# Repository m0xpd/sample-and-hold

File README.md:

# S&H
A Sample and Hold for Eurorack, based on the LF398

This repository describes a simple sample & hold module, developed for electronic synthesisers, in Eurorack format, based on the
[LF398](https://www.ti.com/lit/gpn/lf398-n) device. 

**Functional Description**

S&H is designed to be a simple, "no frills" sample and hold. It just detects a rising edge on the TRIGGER input and samples the 
voltage applied to INPUT at the point of this edge and holds on OUTPUT until the next triggering event. There is a GATE output, 
which is asserted for as long as the TRIGGER signal is high and an internal clock, which generates a trigger stream normalled 
to the edge detection circuits when nothing else is plugged into the TRIGGER input.

**Licensing**

S&H is published under a Creative Commons BY-SA 4.0 [License](https://github.com/m0xpd/encore/blob/main/LICENSE.txt)

**Implementation**

The system is implemented on a single PCB.

The schematic for the system is linked by the graphic below below (click for the full-size schematic):

**Specifications**

S&H is 6HP wide and extends 30mm behind the front panel (when a standard Eurorack power header is inserted).

S&H draws <9 mA (typically 5mA) from the +12V supply and <6 mA (typically 3mA) from the -12V supply.

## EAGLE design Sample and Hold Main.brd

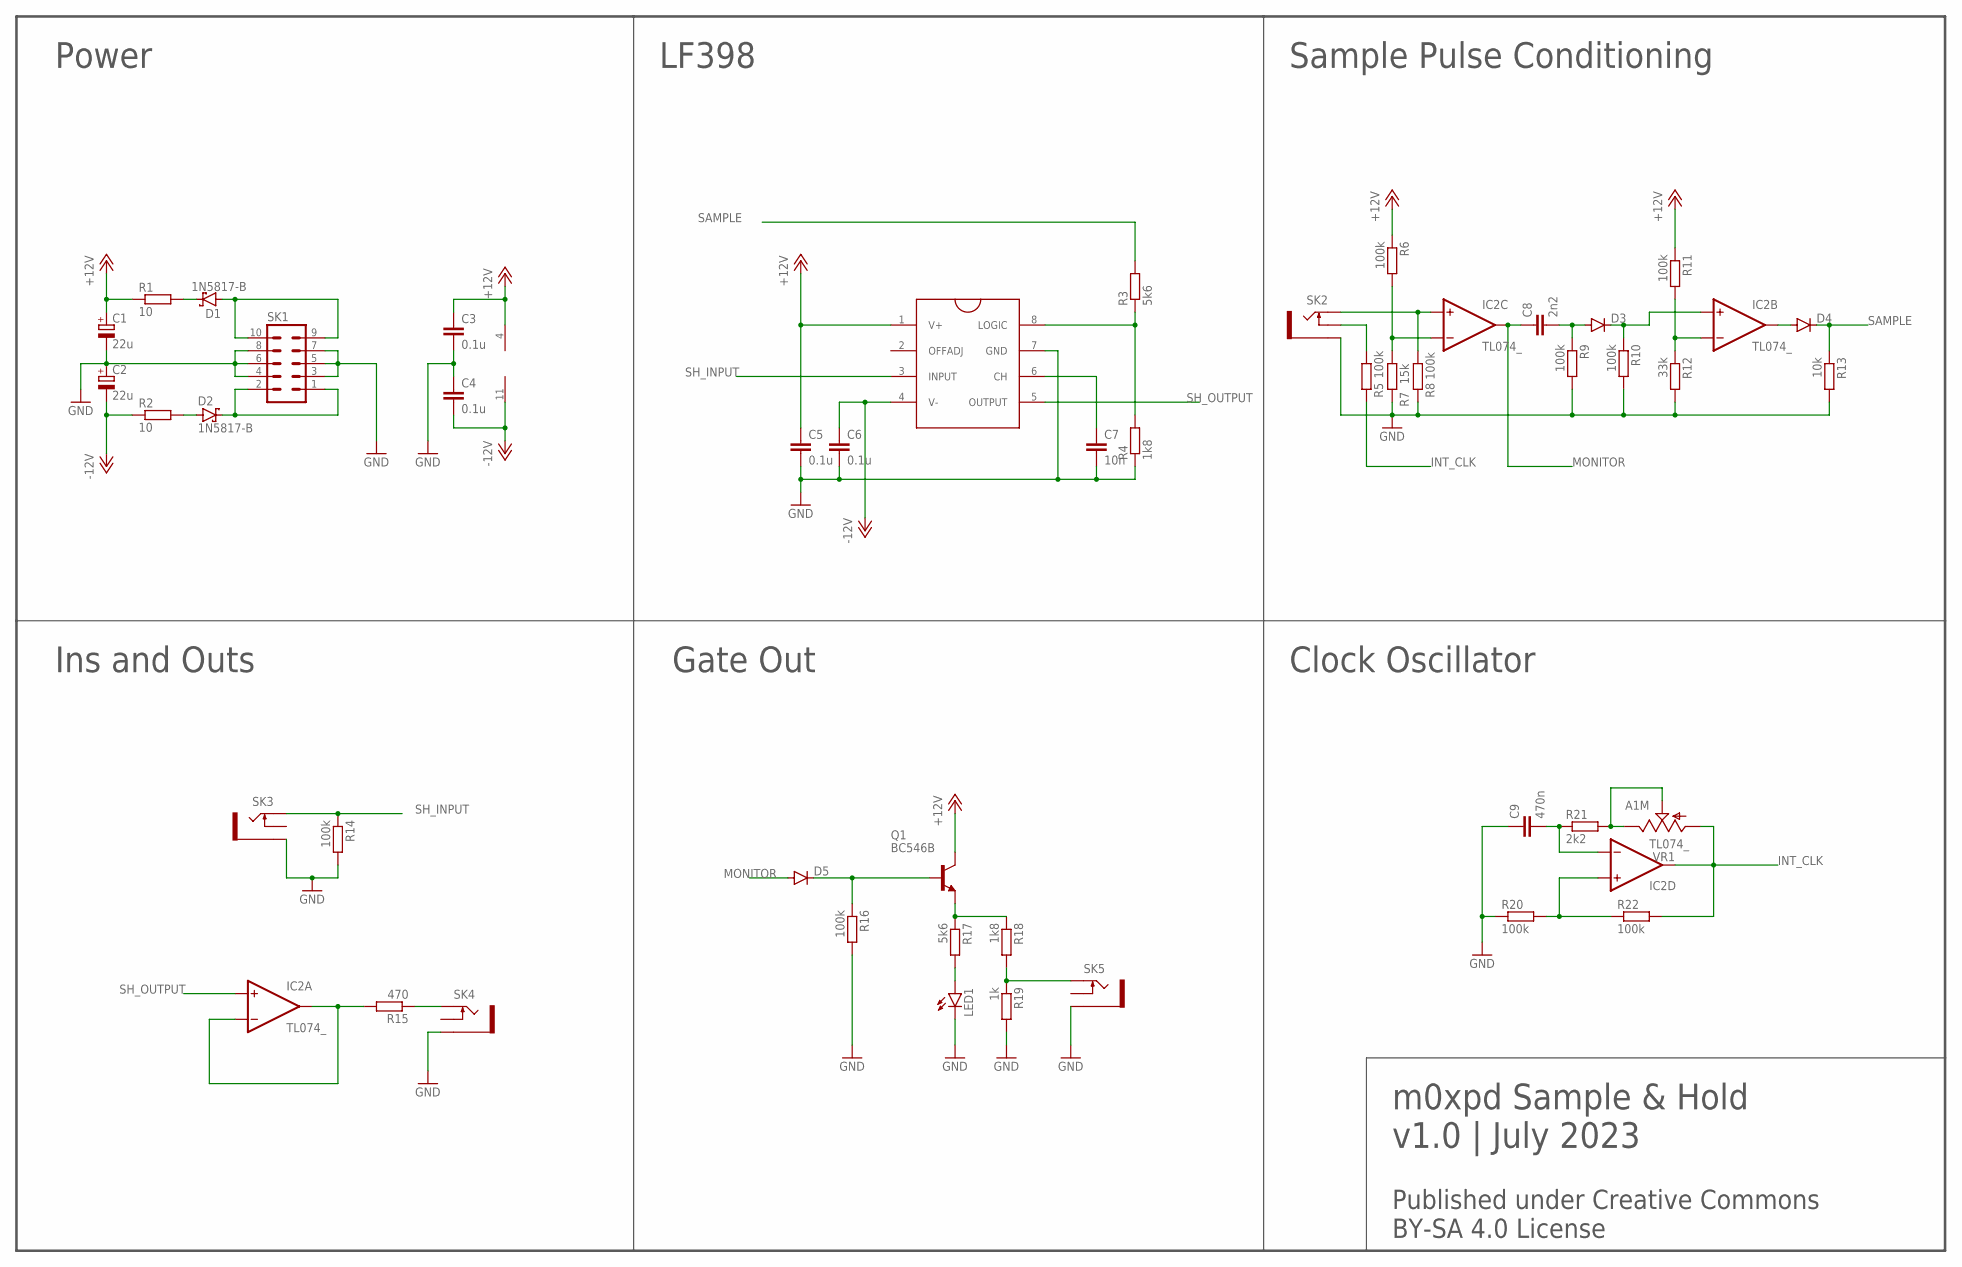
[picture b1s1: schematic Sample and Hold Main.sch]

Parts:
C1, C2: 22u; E2,5-6
C3, C4, C5, C6: 0.1u; C050-024X044
C7: 10n; C050-025X075
C8: 2n2; C050-024X044
C9: 470n; C050-035X075
D1, D2: 1N5817-B; DO41-7.6
D3, D4, D5: 1N4148DO35-7; DO35-7
IC1: LF398; DIL08
IC2: TL074_; DIL14
LED1: LED3MM
Q1: BC546B; TO92-EBC
R1, R2: 10; 0204/7
R3, R17: 5k6; 0204/7
R4, R18: 1k8; 0204/7
R5, R6, R8, R9, R10, R11, R14, R16, R20, R22: 100k; 0204/7
R7: 15k; 0204/7
R12: 33k; 0204/7
R13: 10k; 0204/7
R15: 470; 0204/7
R19: 1k; 0204/7
R21: 2k2; 0204/7
SK1: EURO_POWER_HEADERFAT_PADS; EURO_PWR_HEADER_FAT
SK2, SK3, SK4, SK5: THONKICONNNEW; WQP-PJ301M-12_JACK
VR1: A1M; 9MM_SNAP-IN_POT

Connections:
+12V: C1.+, C3.1, C5.1, IC1.1 (V+), IC2.4 (V+), Q1.C, R1.1, R6.1, R11.1
-12V: C2.-, C4.2, C6.1, IC1.4 (V-), IC2.11 (V-), R2.1
GND: C1.-, C2.+, C3.2, C4.1, C5.2, C6.2, C7.2, C9.1, IC1.7 (GND), LED1.K (C), R4.1, R7.2, R8.2, R9.2, R10.2, R12.2, R13.2, R14.2, R16.2, R19.2, R20.1, SK1.3, SK1.4, SK1.5, SK1.6, SK1.7, SK1.8, SK2.P$3_SLEEVE (SLEEVE), SK3.P$3_SLEEVE (SLEEVE), SK4.P$3_SLEEVE (SLEEVE), SK5.P$3_SLEEVE (SLEEVE)
INT_CLK: IC2.14 (OUT), R5.2, R22.2, VR1.1 (A)
MONITOR: C8.1, D5.A, IC2.8 (OUT)
unnamed: IC2.1 (OUT), IC2.2 (-IN), R15.2
unnamed: IC2.9 (-IN), R6.2, R7.1
unnamed: R15.1, SK4.P$1_TIP (TIP)
unnamed: C7.1, IC1.6 (CH)
unnamed: IC2.10 (+IN), R8.1, SK2.P$1_TIP (TIP)
unnamed: IC1.8 (LOGIC), R3.1, R4.2
unnamed: Q1.E, R17.1, R18.1
unnamed: C8.2, D3.A, R9.1
unnamed: D3.C, IC2.5 (+IN), R10.1
unnamed: LED1.A, R17.2
unnamed: IC2.6 (-IN), R11.2, R12.1
unnamed: D4.A, IC2.7 (OUT)
unnamed: C9.2, IC2.13 (-IN), R21.1
unnamed: IC2.12 (+IN), R20.2, R22.1
unnamed: D5.C, Q1.B, R16.1
unnamed: R21.2, VR1.2 (S), VR1.3 (E)
unnamed: R5.1, SK2.P$2_SWITCH (SWITCH)
unnamed: R18.2, R19.1, SK5.P$1_TIP (TIP)
unnamed: D2.C, SK1.1, SK1.2
unnamed: D1.A, SK1.9, SK1.10
unnamed: D1.C, R1.2
unnamed: D2.A, R2.2
SAMPLE: D4.C, R3.2, R13.1
SH_INPUT: IC1.3 (INPUT), R14.1, SK3.P$1_TIP (TIP)
SH_OUTPUT: IC1.5 (OUTPUT), IC2.3 (+IN)

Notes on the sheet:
Power
LF398
Sample Pulse Conditioning
Ins and Outs
Gate Out
Clock Oscillator
m0xpd Sample & Hold
v1.0 | July 2023
Published under Creative Commons BY-SA 4.0 License

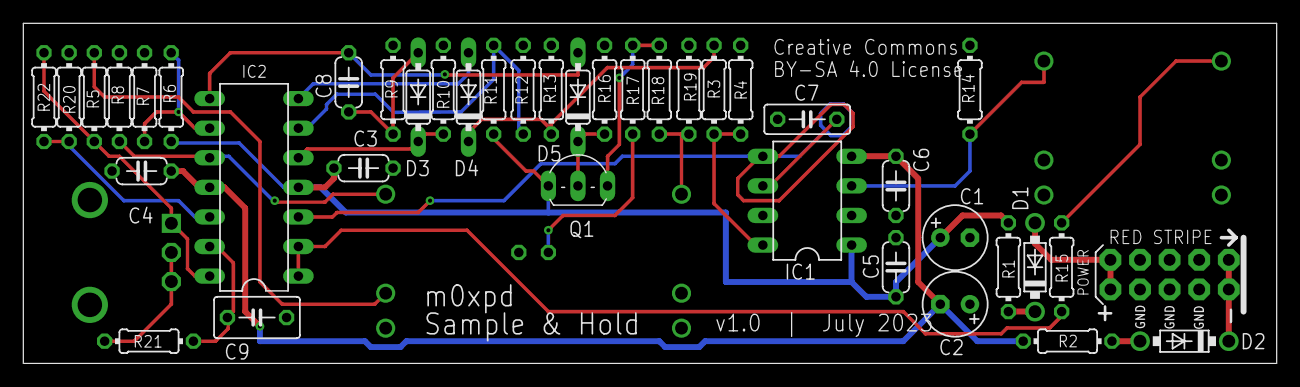
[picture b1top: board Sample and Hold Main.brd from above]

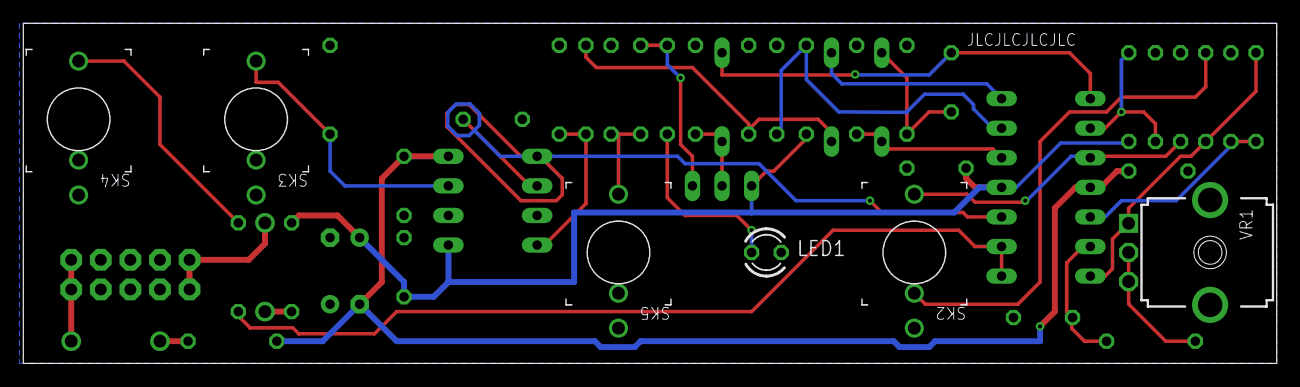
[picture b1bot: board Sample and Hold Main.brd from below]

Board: 2 copper layers, 107.6 x 29.2 mm, 46 parts (6 on the bottom side), 30 nets.

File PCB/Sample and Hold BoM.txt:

Partlist exported from /Users/pauldarlington/Documents/EAGLE/projects/Sample and Hold/Sample and Hold Main.sch at 05/08/2023 07:36

Part Value                     Device                    Package             Description                                       POPULARITY SPICEPREFIX
C1   22u                       CPOL-EUE2.5-6             E2,5-6              POLARIZED CAPACITOR, European symbol              26         C          
C2   22u                       CPOL-EUE2.5-6             E2,5-6              POLARIZED CAPACITOR, European symbol              26         C          
C3   0.1u                      C-EU050-024X044           C050-024X044        CAPACITOR, European symbol                        33         C          
C4   0.1u                      C-EU050-024X044           C050-024X044        CAPACITOR, European symbol                        33         C          
C5   0.1u                      C-EU050-024X044           C050-024X044        CAPACITOR, European symbol                        33         C          
C6   0.1u                      C-EU050-024X044           C050-024X044        CAPACITOR, European symbol                        33         C          
C7   10n                       C-EU050-025X075           C050-025X075        CAPACITOR, European symbol                        29         C          
C8   2n2                       C-EU050-024X044           C050-024X044        CAPACITOR, European symbol                        33         C          
C9   470n                      C-EU050-035X075           C050-035X075        CAPACITOR, European symbol                        2          C          
D1   1N5817-B                  1N5817-B                  DO41-7.6            1.0A SCHOTTKY BARRIER RECTIFIER                   0                     
D2   1N5817-B                  1N5817-B                  DO41-7.6            1.0A SCHOTTKY BARRIER RECTIFIER                   0                     
D3   1N4148DO35-7              1N4148DO35-7              DO35-7              DIODE                                             58                    
D4   1N4148DO35-7              1N4148DO35-7              DO35-7              DIODE                                             58                    
D5   1N4148DO35-7              1N4148DO35-7              DO35-7              DIODE                                             58                    
IC1  LF398                     LF398                     DIL08               Sample and Hold device                                                  
IC2  TL074_                    TL074_                    DIL14               Generic Quad Op Amp                                                     
LED1                           LED3MM                    LED3MM              LED                                               97                    
Q1   BC546B                    BC546B                    TO92-EBC            NPN Transistor                                    0                     
R1   10                        R-EU_0204/7               0204/7              RESISTOR, European symbol                         79         R          
R2   10                        R-EU_0204/7               0204/7              RESISTOR, European symbol                         79         R          
R3   5k6                       R-EU_0204/7               0204/7              RESISTOR, European symbol                         79         R          
R4   1k8                       R-EU_0204/7               0204/7              RESISTOR, European symbol                         79         R          
R5   100k                      R-EU_0204/7               0204/7              RESISTOR, European symbol                         79         R          
R6   100k                      R-EU_0204/7               0204/7              RESISTOR, European symbol                         79         R          
R7   15k                       R-EU_0204/7               0204/7              RESISTOR, European symbol                         79         R          
R8   100k                      R-EU_0204/7               0204/7              RESISTOR, European symbol                         79         R          
R9   100k                      R-EU_0204/7               0204/7              RESISTOR, European symbol                         79         R          
R10  100k                      R-EU_0204/7               0204/7              RESISTOR, European symbol                         79         R          
R11  100k                      R-EU_0204/7               0204/7              RESISTOR, European symbol                         79         R          
R12  33k                       R-EU_0204/7               0204/7              RESISTOR, European symbol                         79         R          
R13  10k                       R-EU_0204/7               0204/7              RESISTOR, European symbol                         79         R          
R14  100k                      R-EU_0204/7               0204/7              RESISTOR, European symbol                         79         R          
R15  470                       R-EU_0204/7               0204/7              RESISTOR, European symbol                         79         R          
R16  100k                      R-EU_0204/7               0204/7              RESISTOR, European symbol                         79         R          
R17  5k6                       R-EU_0204/7               0204/7              RESISTOR, European symbol                         79         R          
R18  1k8                       R-EU_0204/7               0204/7              RESISTOR, European symbol                         79         R          
R19  1k                        R-EU_0204/7               0204/7              RESISTOR, European symbol                         79         R          
R20  100k                      R-EU_0204/7               0204/7              RESISTOR, European symbol                         79         R          
R21  2k2                       R-EU_0204/7               0204/7              RESISTOR, European symbol                         79         R          
R22  100k                      R-EU_0204/7               0204/7              RESISTOR, European symbol                         79         R          
SK1  EURO_POWER_HEADERFAT_PADS EURO_POWER_HEADERFAT_PADS EURO_PWR_HEADER_FAT Power Header                                                            
SK2  THONKICONNNEW             THONKICONNNEW             WQP-PJ301M-12_JACK  3.5mm socket for Eurorack modular synths                                
SK3  THONKICONNNEW             THONKICONNNEW             WQP-PJ301M-12_JACK  3.5mm socket for Eurorack modular synths                                
SK4  THONKICONNNEW             THONKICONNNEW             WQP-PJ301M-12_JACK  3.5mm socket for Eurorack modular synths                                
SK5  THONKICONNNEW             THONKICONNNEW             WQP-PJ301M-12_JACK  3.5mm socket for Eurorack modular synths                                
VR1  A1M                       9MM_SNAP-IN_POT_          9MM_SNAP-IN_POT     9mm vertical snap-in pot, Alpha / Panasonic style

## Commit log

2023-08-05 Rename Sample and Hold BoM.txt to PCB/Sample and Hold BoM.txt
2023-08-05 Rename Sample and Hold Main.brd to PCB/Sample and Hold Main.brd
2023-08-05 Rename Sample and Hold Main.sch to PCB/Sample and Hold Main.sch
2023-08-05 Rename Sample & Hold.kicad_pcb to FrontPanel/Sample & Hold.kicad_pcb
2023-08-05 Rename Sample & Hold.kicad_pro to FrontPanel/Sample & Hold.kicad_pro
2023-08-05 Rename Sample & Hold.kicad_sch to FrontPanel/Sample & Hold.kicad_sch
